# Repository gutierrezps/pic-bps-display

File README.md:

# PIC Bench Power Supply display

This is a volt/ammeter display for bench power supplies, based on PIC18F2550.
It is originally designed as a replacement for old power supplies whose displays
are damaged.

Firmware is developed using MPLAB XC8 Compiler (through MPLAB X IDE), based
on some of [my own libraries].

Schematics and PCB are designed using [KiCAD].

[my own libraries]: https://github.com/gutierrezps/PIC18F2550_Libraries
[KiCAD]: https://kicad.org/

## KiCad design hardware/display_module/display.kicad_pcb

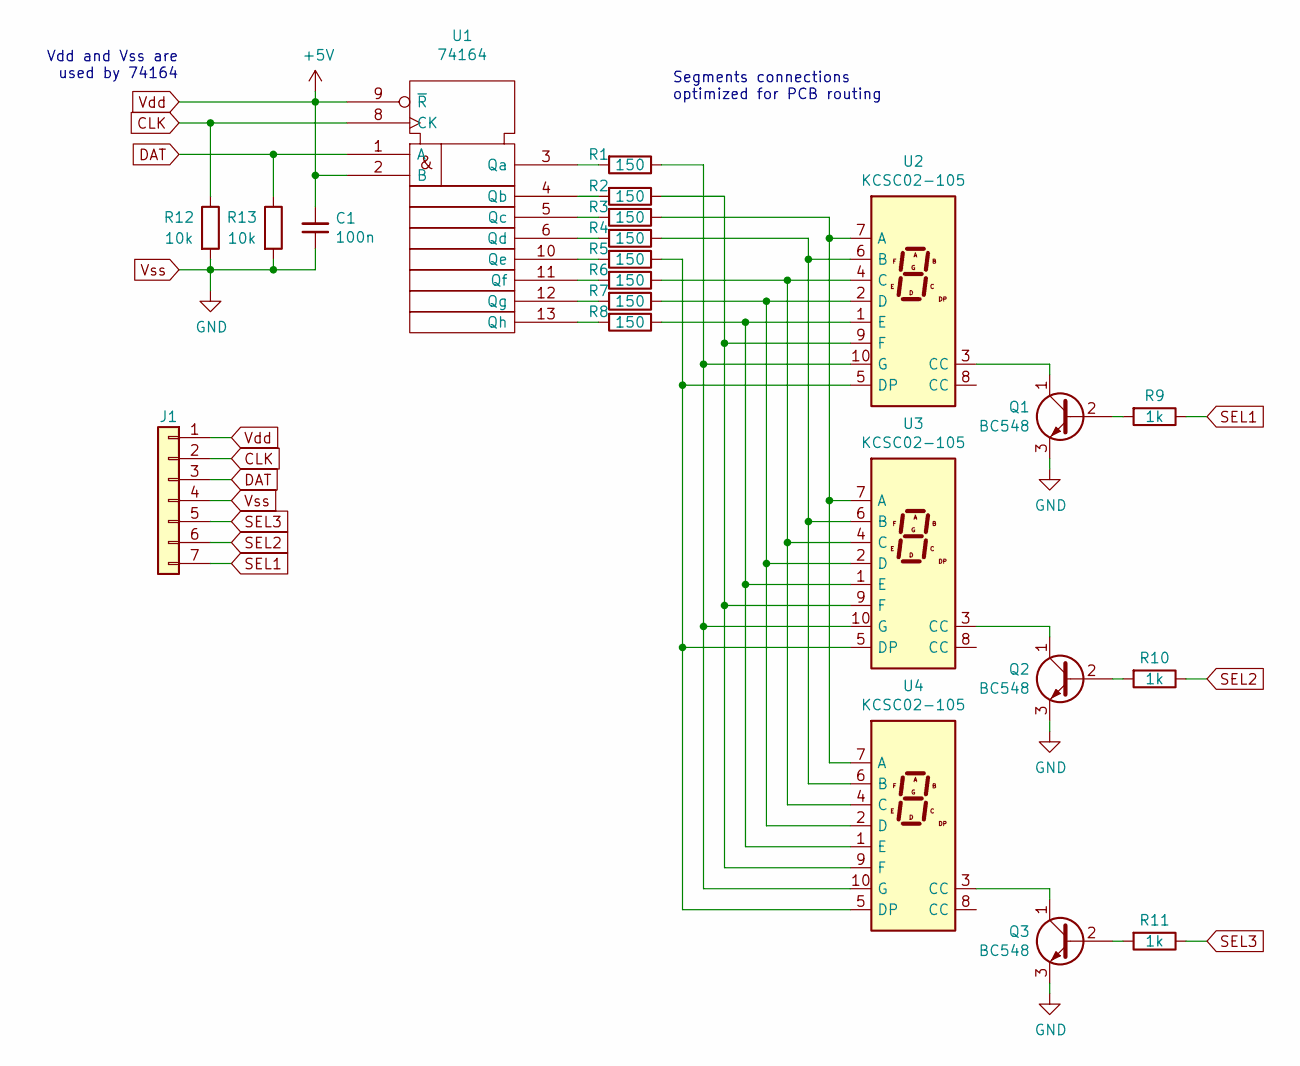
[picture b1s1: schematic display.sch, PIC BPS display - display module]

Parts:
C1: 100n; C_0805_2012Metric_Pad1.15x1.40mm_HandSolder
J1: Conn_01x07; PinHeader_1x07_P2.54mm_Vertical
Q1, Q2, Q3: BC548; TO-92_Inline_Wide
R1, R2, R3, R4, R5, R6, R7, R8: 150; R_Axial_DIN0207_L6.3mm_D2.5mm_P10.16mm_Horizontal
R9, R10, R11: 1k; R_Axial_DIN0207_L6.3mm_D2.5mm_P10.16mm_Horizontal
R12, R13: 10k; R_Axial_DIN0207_L6.3mm_D2.5mm_P10.16mm_Horizontal
U1: 74164; DIP-14_W7.62mm_LongPads
U2, U3, U4: KCSC02-105; 7SegmentLED_LTS6760_LTS6780

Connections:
CLK: J1.2, R12.1, U1.8 (CK)
DAT: J1.3, R13.1, U1.1 (A)
unnamed: Q1.1 (C), U2.3 (CC)
unnamed: Q1.2 (B), R9.2
unnamed: Q2.1 (C), U3.3 (CC)
unnamed: Q2.2 (B), R10.2
unnamed: Q3.1 (C), U4.3 (CC)
unnamed: Q3.2 (B), R11.2
unnamed: R1.1, U2.10 (G), U3.10 (G), U4.10 (G)
unnamed: R1.2, U1.3 (Qa)
unnamed: R2.1, U2.9 (F), U3.9 (F), U4.9 (F)
unnamed: R2.2, U1.4 (Qb)
unnamed: R3.1, U2.7 (A), U3.7 (A), U4.7 (A)
unnamed: R3.2, U1.5 (Qc)
unnamed: R4.1, U2.6 (B), U3.6 (B), U4.6 (B)
unnamed: R4.2, U1.6 (Qd)
unnamed: R5.1, U2.5 (DP), U3.5 (DP), U4.5 (DP)
unnamed: R5.2, U1.10 (Qe)
unnamed: R6.1, U2.4 (C), U3.4 (C), U4.4 (C)
unnamed: R6.2, U1.11 (Qf)
unnamed: R7.1, U2.2 (D), U3.2 (D), U4.2 (D)
unnamed: R7.2, U1.12 (Qg)
unnamed: R8.1, U2.1 (E), U3.1 (E), U4.1 (E)
unnamed: R8.2, U1.13 (Qh)
SEL1: J1.7, R9.1
SEL2: J1.6, R10.1
SEL3: J1.5, R11.1
Vdd: C1.2, J1.1, U1.2 (B), U1.9 (~R), U1.14 (Vdd)
Vss: C1.1, J1.4, Q1.3 (E), Q2.3 (E), Q3.3 (E), R12.2, R13.2, U1.7 (Vss)

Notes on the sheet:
Segments connections optimized for PCB routing
Vdd and Vss are used by 74164

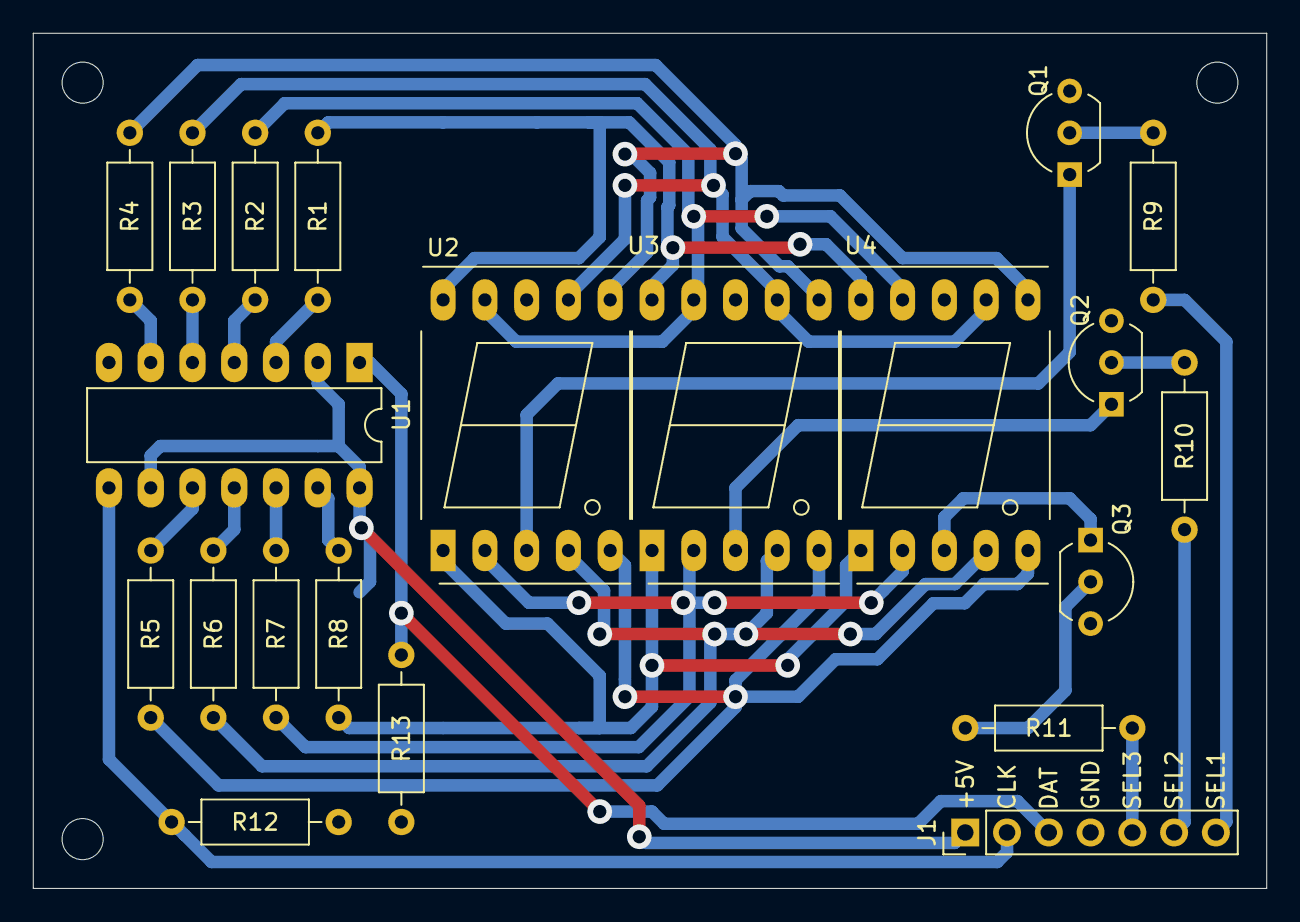
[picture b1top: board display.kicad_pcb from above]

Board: 2 copper layers, 75.0 x 52.0 mm, 22 parts (1 on the bottom side), 29 nets.

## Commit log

2021-03-05 Add readme
2021-03-05 Add firmware files
2021-03-10 Add display module hardware files
